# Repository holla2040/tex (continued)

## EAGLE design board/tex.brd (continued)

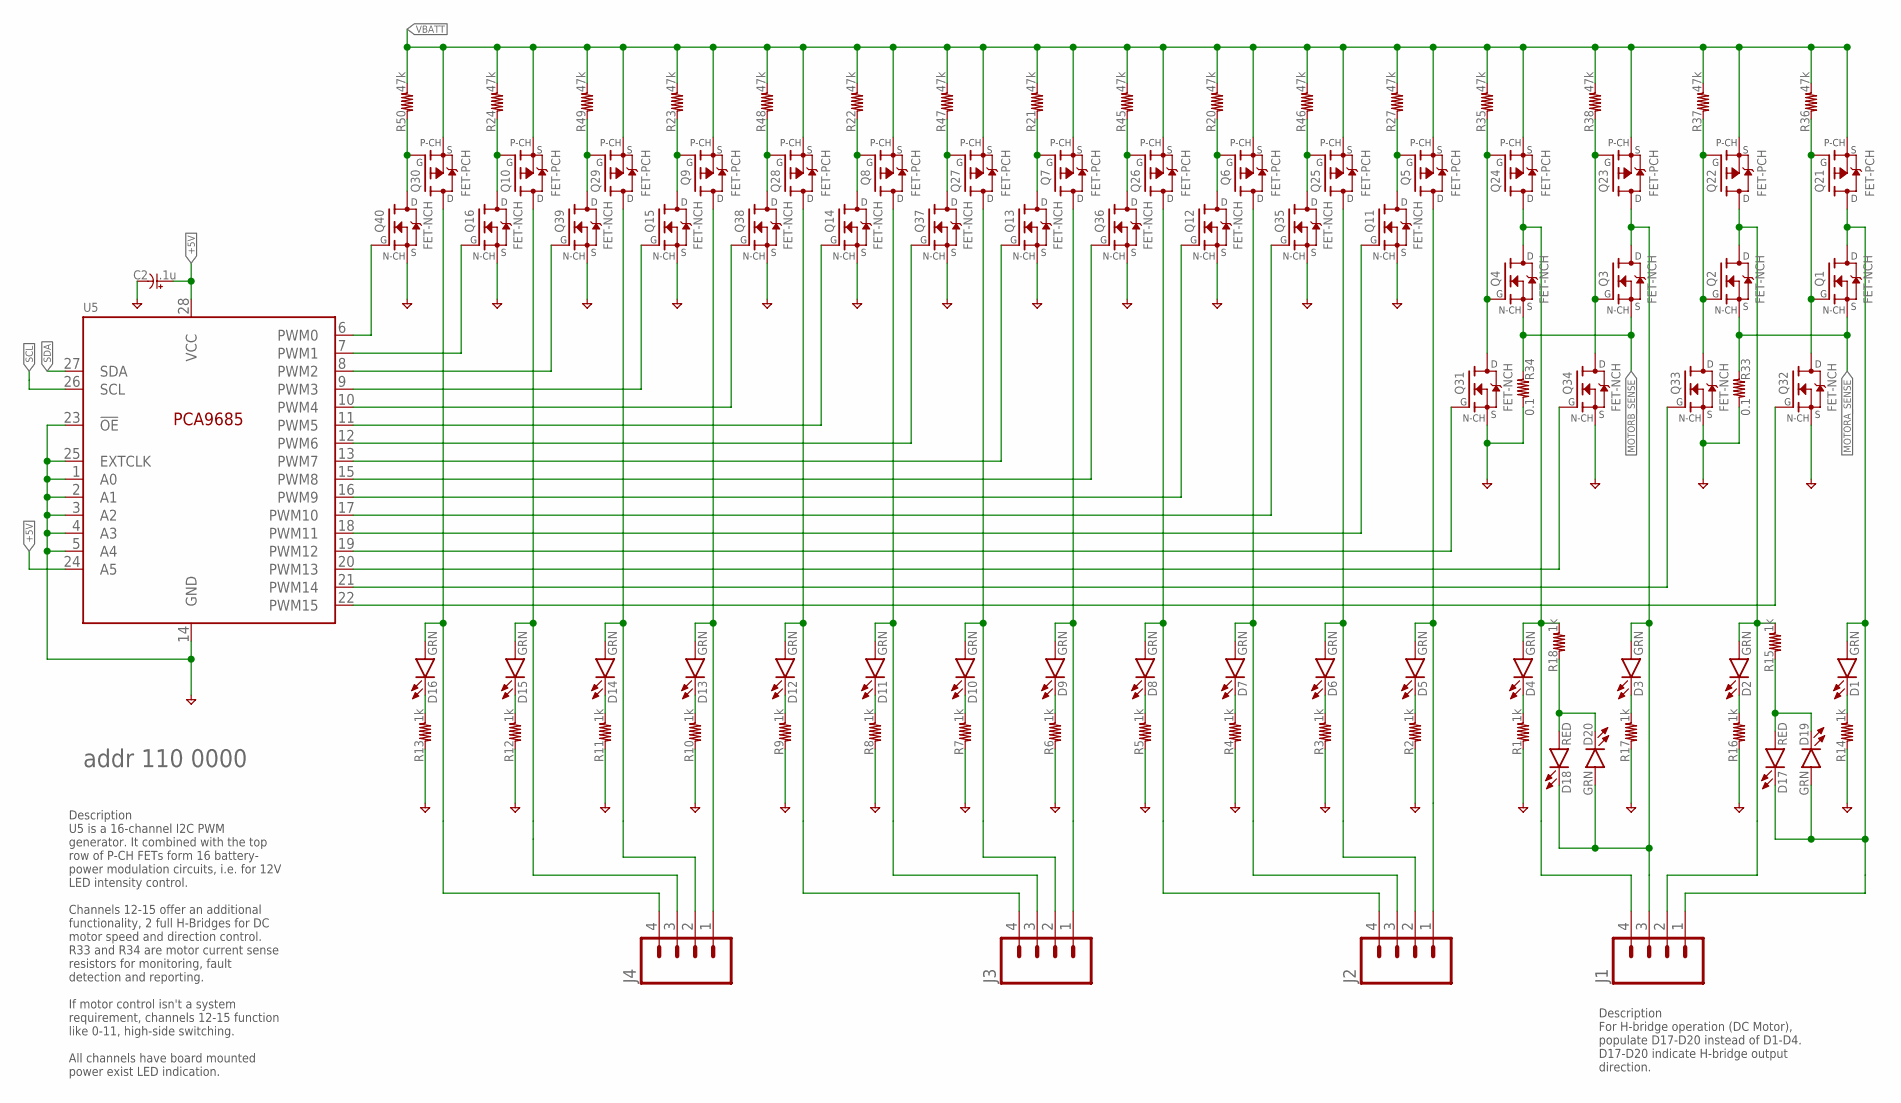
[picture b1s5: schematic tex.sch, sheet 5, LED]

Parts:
C2: .1u; C0603
D1, D2, D3, D4, D5, D6, D7, D8, D9, D10, D11, D12, D13, D14, D15, D16, D19, D20: GRN; LED0603
D17, D18: RED; LED0603
J1, J2, J3, J4: CONN-04-PLUGIN-SCREW; CONN-3.81MM-KF2EDG-4
Q1, Q2, Q3, Q4: FET-NCH; TO252
Q5, Q6, Q7, Q8, Q9, Q10, Q21, Q22, Q23, Q24, Q25, Q26, Q27, Q28, Q29, Q30: FET-PCH; TO252
Q11, Q12, Q13, Q14, Q15, Q16, Q31, Q32, Q33, Q34, Q35, Q36, Q37, Q38, Q39, Q40: FET-NCH; SOT23-3
R1, R2, R3, R4, R5, R6, R7, R8, R9, R10, R11, R12, R13, R14, R15, R16, R17, R18: 1k; R0603
R20, R21, R22, R23, R24, R27, R35, R36, R37, R38, R45, R46, R47, R48, R49, R50: 47k; R0603
R33, R34: 0.1; R1210
U5: PCA9685; TSSOP28

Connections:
+5V: C2.1, U5.24 (A5), U5.28 (VCC); also elsewhere on the board
GND: C2.2, Q11.2 (S), Q12.2 (S), Q13.2 (S), Q14.2 (S), Q15.2 (S), Q16.2 (S), Q31.2 (S), Q32.2 (S), Q33.2 (S), Q34.2 (S), Q35.2 (S), Q36.2 (S), Q37.2 (S), Q38.2 (S), Q39.2 (S), Q40.2 (S), R1.1, R2.1, R3.1, R4.1, R5.1, R6.1, R7.1, R8.1, R9.1, R10.1, R11.1, R12.1, R13.1, R14.1, R16.1, R17.1, R33.2, R34.2, U5.1 (A0), U5.2 (A1), U5.3 (A2), U5.4 (A3), U5.5 (A4), U5.14 (GND), U5.23 (!OE), U5.25 (EXTCLK); also elsewhere on the board
MOTORA_SENSE: Q1.2 (S), Q2.2 (S), R33.1; also elsewhere on the board
MOTORB_SENSE: Q3.2 (S), Q4.2 (S), R34.1; also elsewhere on the board
unnamed: Q40.1 (G), U5.6 (PWM0)
unnamed: Q6.1 (G), Q12.3 (D), R20.1
unnamed: Q26.1 (G), Q36.3 (D), R45.1
unnamed: Q7.1 (G), Q13.3 (D), R21.1
unnamed: Q27.1 (G), Q37.3 (D), R47.1
unnamed: Q8.1 (G), Q14.3 (D), R22.1
unnamed: Q28.1 (G), Q38.3 (D), R48.1
unnamed: Q9.1 (G), Q15.3 (D), R23.1
unnamed: Q29.1 (G), Q39.3 (D), R49.1
unnamed: Q10.1 (G), Q16.3 (D), R24.1
unnamed: Q30.1 (G), Q40.3 (D), R50.1
unnamed: Q16.1 (G), U5.7 (PWM1)
unnamed: Q39.1 (G), U5.8 (PWM2)
unnamed: Q15.1 (G), U5.9 (PWM3)
unnamed: Q38.1 (G), U5.10 (PWM4)
unnamed: Q14.1 (G), U5.11 (PWM5)
unnamed: Q37.1 (G), U5.12 (PWM6)
unnamed: Q13.1 (G), U5.13 (PWM7)
unnamed: Q36.1 (G), U5.15 (PWM8)
unnamed: Q12.1 (G), U5.16 (PWM9)
unnamed: D2.A, J1.2, Q2.3 (D), Q22.3 (D), R15.2
unnamed: Q2.1 (G), Q22.1 (G), Q33.3 (D), R37.1
unnamed: D1.A, D17.C, D19.A, J1.1, Q1.3 (D), Q21.3 (D)
unnamed: Q1.1 (G), Q21.1 (G), Q32.3 (D), R36.1
unnamed: Q32.1 (G), U5.22 (PWM15)
unnamed: Q33.1 (G), U5.21 (PWM14)
unnamed: D4.A, J1.4, Q4.3 (D), Q24.3 (D), R18.2
unnamed: Q4.1 (G), Q24.1 (G), Q31.3 (D), R35.1
unnamed: D16.A, J4.4, Q30.3 (D)
unnamed: D15.A, J4.3, Q10.3 (D)
unnamed: D14.A, J4.2, Q29.3 (D)
unnamed: D13.A, J4.1, Q9.3 (D)
unnamed: D12.A, J3.4, Q28.3 (D)
unnamed: D11.A, J3.3, Q8.3 (D)
unnamed: D10.A, J3.2, Q27.3 (D)
unnamed: D9.A, J3.1, Q7.3 (D)
unnamed: D8.A, J2.4, Q26.3 (D)
unnamed: D7.A, J2.3, Q6.3 (D)
unnamed: D13.C, R10.2
unnamed: D12.C, R9.2
unnamed: D1.C, R14.2
unnamed: D2.C, R16.2
unnamed: D3.C, R17.2
unnamed: D4.C, R1.2
unnamed: D14.C, R11.2
unnamed: D15.C, R12.2
unnamed: D16.C, R13.2
unnamed: D3.A, D18.C, D20.A, J1.3, Q3.3 (D), Q23.3 (D)
unnamed: Q3.1 (G), Q23.1 (G), Q34.3 (D), R38.1
unnamed: Q34.1 (G), U5.20 (PWM13)
unnamed: Q31.1 (G), U5.19 (PWM12)
unnamed: D18.A, D20.C, R18.1
unnamed: Q35.1 (G), U5.17 (PWM10)
unnamed: Q11.1 (G), U5.18 (PWM11)
unnamed: D17.A, D19.C, R15.1
unnamed: D6.A, J2.2, Q25.3 (D)
unnamed: D5.A, J2.1, Q5.3 (D)
unnamed: Q5.1 (G), Q11.3 (D), R27.1
unnamed: Q25.1 (G), Q35.3 (D), R46.1
unnamed: D5.C, R2.2
unnamed: D6.C, R3.2
unnamed: D7.C, R4.2
unnamed: D8.C, R5.2
unnamed: D9.C, R6.2
unnamed: D10.C, R7.2
unnamed: D11.C, R8.2
SCL: U5.26 (SCL); also elsewhere on the board
SDA: U5.27 (SDA); also elsewhere on the board
VBATT: Q5.2 (S), Q6.2 (S), Q7.2 (S), Q8.2 (S), Q9.2 (S), Q10.2 (S), Q21.2 (S), Q22.2 (S), Q23.2 (S), Q24.2 (S), Q25.2 (S), Q26.2 (S), Q27.2 (S), Q28.2 (S), Q29.2 (S), Q30.2 (S), R20.2, R21.2, R22.2, R23.2, R24.2, R27.2, R35.2, R36.2, R37.2, R38.2, R45.2, R46.2, R47.2, R48.2, R49.2, R50.2; also elsewhere on the board

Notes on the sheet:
addr 110 0000
Description U5 is a 16-channel I2C PWM generator. It combined with the top row of P-CH FETs form 16 battery- power modulation circuits, i.e. for 12V LED intensity control. Channels 12-15 offer an additional functionality, 2 full H-Bridges for DC motor speed and direction control. R33 and R34 are mo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
Description For H-bridge operation (DC Motor), populate D17-D20 instead of D1-D4. D17-D20 indicate H-bridge output direction.

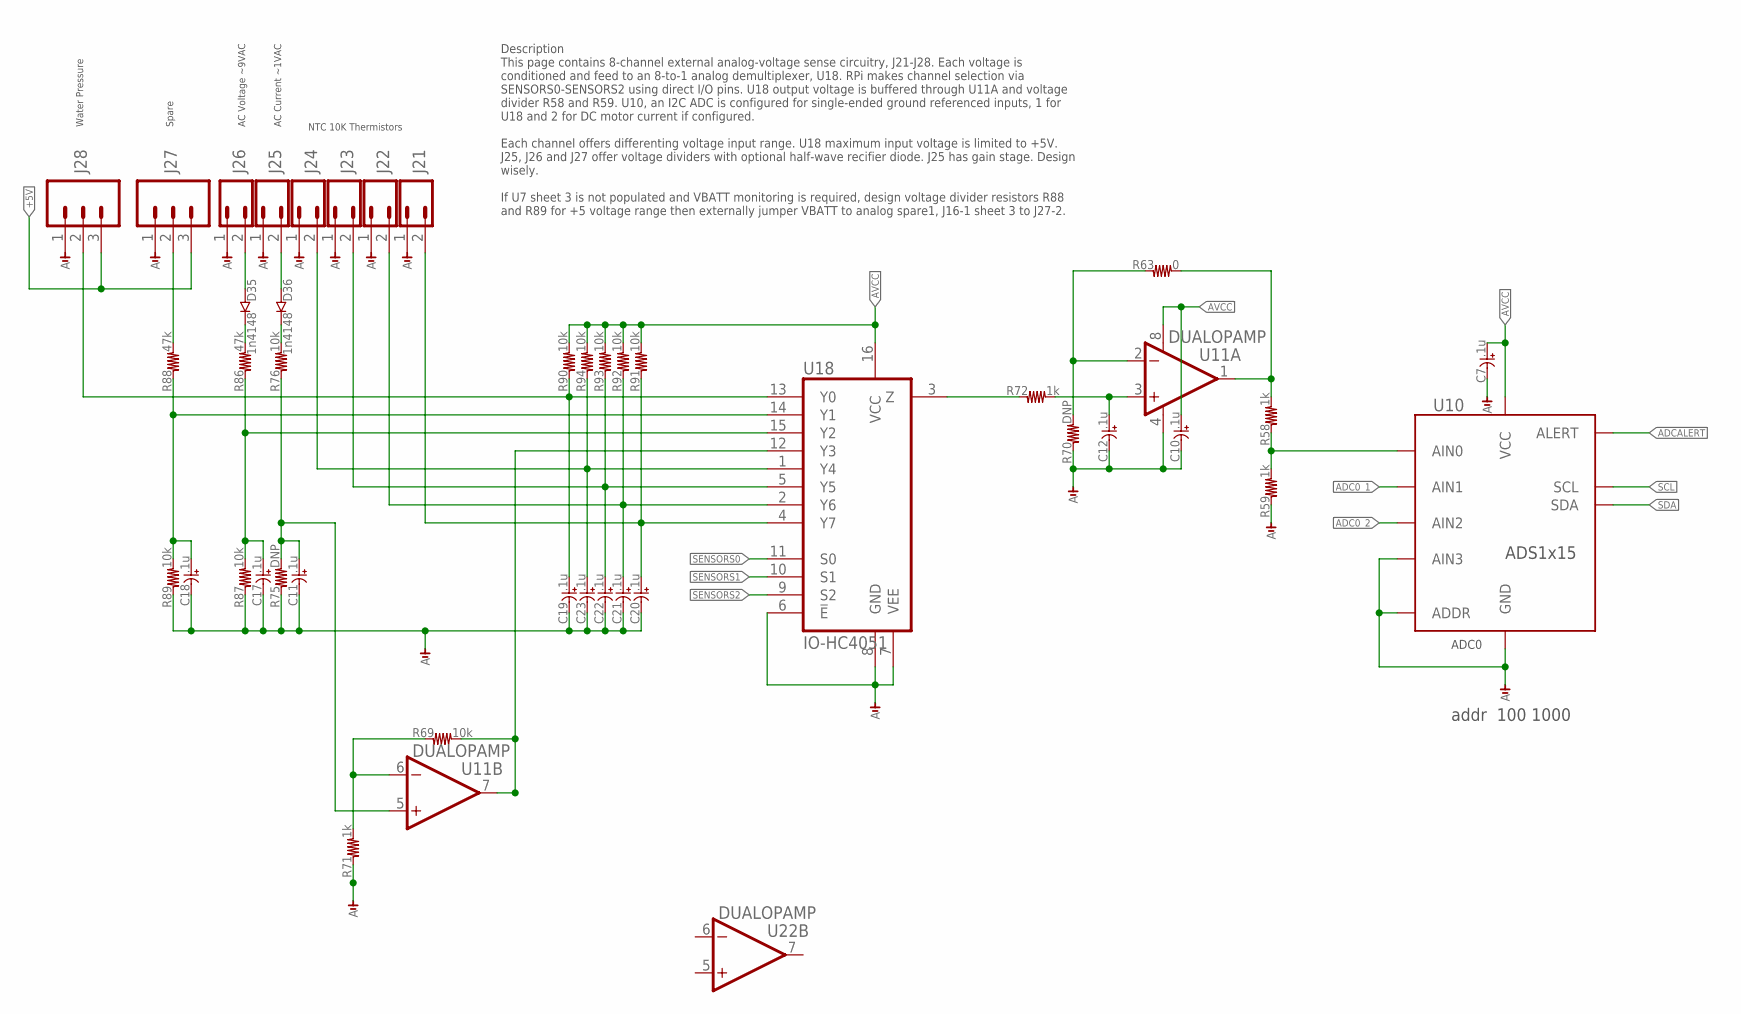
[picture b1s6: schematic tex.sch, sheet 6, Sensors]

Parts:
C7, C10, C11, C12, C17, C18, C19, C20, C21, C22, C23: .1u; C0603
D35, D36: 1n4148; SOD-523
J21, J22, J23, J24, J25, J26: CONN-02-PLUGIN-SCREW; CONN-3.81MM-KF2EDG-2
J27, J28: CONN-03-PLUGIN-SCREW; CONN-3.81MM-KF2EDG-3
R58, R59, R71, R72: 1k; R0603
R63: 0; R0603
R69, R76, R87, R89, R90, R91, R92, R93, R94: 10k; R0603
R70, R75: DNP; R0603
R86, R88: 47k; R0603
U10: ADS1x15; MSOP10_0.5
U11, U22: DUALOPAMP; SO08
U18: IO-HC4051; SO16

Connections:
+5V: J27.3, J28.3; also elsewhere on the board
ADC0_1: U10.5 (AIN1); also elsewhere on the board
ADC0_2: U10.6 (AIN2); also elsewhere on the board
ADCALERT: U10.2 (ALERT); also elsewhere on the board
AGND: C7.2, C10.2, C11.2, C12.2, C17.2, C18.2, C19.2, C20.2, C21.2, C22.2, C23.2, J21.1, J22.1, J23.1, J24.1, J25.1, J26.1, J27.1, J28.1, R59.1, R70.1, R71.1, R75.1, R87.1, R89.1, U10.1 (ADDR), U10.3 (GND), U10.7 (AIN3), U11.4 (V-), U18.6 (!E), U18.7 (VEE), U18.8 (GND); also elsewhere on the board
AVCC: C7.1, C10.1, R90.2, R91.2, R92.2, R93.2, R94.2, U10.8 (VCC), U11.8 (V+), U18.16 (VCC); also elsewhere on the board
unnamed: D35.C, R86.2
unnamed: D35.A, J26.2
unnamed: D36.C, R76.2
unnamed: D36.A, J25.2
unnamed: J27.2, R88.2
unnamed: R63.1, R70.2, U11.2 (-IN)
unnamed: R69.1, R71.2, U11.6 (-IN)
unnamed: C12.1, R72.2, U11.3 (+IN)
unnamed: C19.1, J28.2, R90.1, U18.13 (Y0)
unnamed: C18.1, R88.1, R89.2, U18.14 (Y1)
unnamed: C17.1, R86.1, R87.2, U18.15 (Y2)
unnamed: C11.1, R75.2, R76.1, U11.5 (+IN)
unnamed: C23.1, J24.2, R94.1, U18.1 (Y4)
unnamed: C22.1, J23.2, R93.1, U18.5 (Y5)
unnamed: C21.1, J22.2, R92.1, U18.2 (Y6)
unnamed: C20.1, J21.2, R91.1, U18.4 (Y7)
unnamed: R58.2, R63.2, U11.1 (OUT)
unnamed: R72.1, U18.3 (Z)
unnamed: R58.1, R59.2, U10.4 (AIN0)
unnamed: R69.2, U11.7 (OUT), U18.12 (Y3)
SCL: U10.10 (SCL); also elsewhere on the board
SDA: U10.9 (SDA); also elsewhere on the board
SENSORS0: U18.11 (S0); also elsewhere on the board
SENSORS1: U18.10 (S1); also elsewhere on the board
SENSORS2: U18.9 (S2); also elsewhere on the board
V+: U22.8 (V+)
V-: U22.4 (V-)

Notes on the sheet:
ADC0
NTC 10K Thermistors
Water Pressure
Spare
AC Voltage ~9VAC
AC Current ~1VAC
addr 100 1000
Description This page contains 8-channel external analog-voltage sense circuitry, J21-J28. Each voltage is conditioned and feed to an 8-to-1 analog demultiplexer, U18. RPi makes channel selection via SENSORS0-SENSORS2 using direct I/O pins. U18 output voltage is buffered through U11A and voltage di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

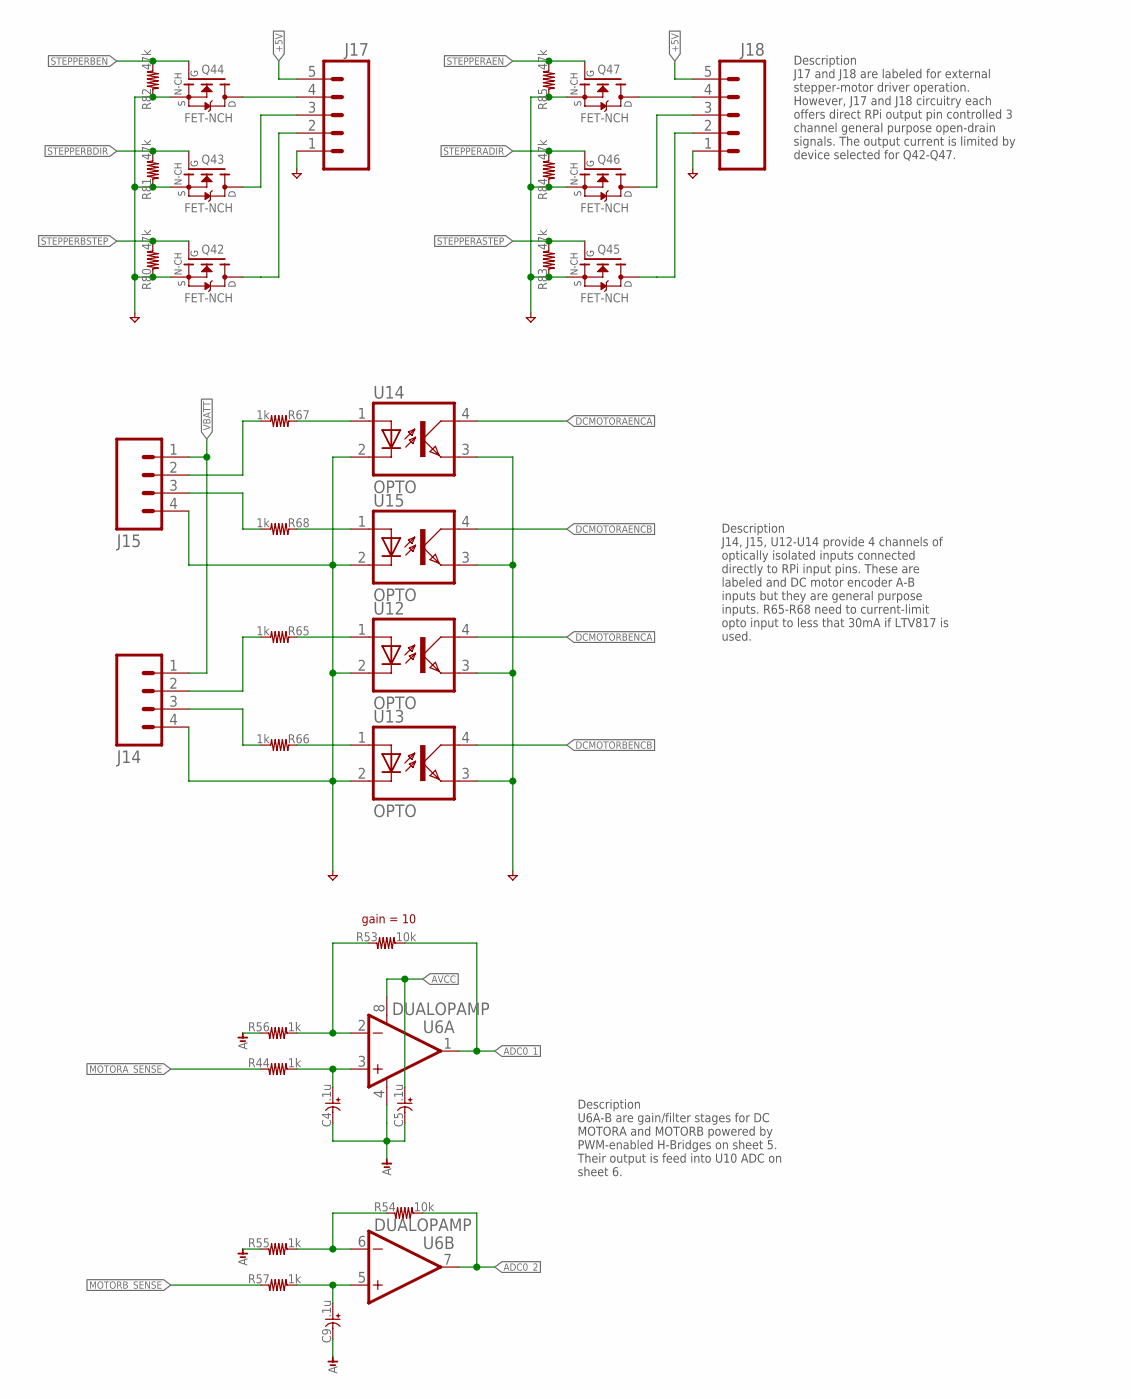
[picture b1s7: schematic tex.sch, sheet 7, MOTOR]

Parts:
C4, C5, C9: .1u; C0603
J14, J15: CONN-04-PLUGIN-SCREW; CONN-3.81MM-KF2EDG-4
J17, J18: CONN-05-PLUGIN-SCREW; CONN-3.81MM-KF2EDG-5
Q42, Q43, Q44, Q45, Q46, Q47: FET-NCH; SOT23-3
R44, R55, R56, R57, R65, R66, R67, R68: 1k; R0603
R53, R54: 10k; R0603
R80, R81, R82, R83, R84, R85: 47k; R0603
U6: DUALOPAMP; SO08
U12, U13, U14, U15: OPTO; LTV817

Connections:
+5V: J17.5, J18.5; also elsewhere on the board
ADC0_1: R53.2, U6.1 (OUT); also elsewhere on the board
ADC0_2: R54.2, U6.7 (OUT); also elsewhere on the board
AGND: C4.2, C5.2, C9.2, R55.1, R56.1, U6.4 (V-); also elsewhere on the board
AVCC: C5.1, U6.8 (V+); also elsewhere on the board
DCMOTORAENCA: U14.4; also elsewhere on the board
DCMOTORAENCB: U15.4; also elsewhere on the board
DCMOTORBENCA: U12.4; also elsewhere on the board
DCMOTORBENCB: U13.4; also elsewhere on the board
GND: J14.4, J15.4, J17.1, J18.1, Q42.2 (S), Q43.2 (S), Q44.2 (S), Q45.2 (S), Q46.2 (S), Q47.2 (S), R80.1, R81.1, R82.1, R83.1, R84.1, R85.1, U12.2, U12.3, U13.2, U13.3, U14.2, U14.3, U15.2, U15.3; also elsewhere on the board
MOTORA_SENSE: R44.1; also elsewhere on the board
MOTORB_SENSE: R57.1; also elsewhere on the board
unnamed: C4.1, R44.2, U6.3 (+IN)
unnamed: R54.1, R55.2, U6.6 (-IN)
unnamed: R53.1, R56.2, U6.2 (-IN)
unnamed: C9.1, R57.2, U6.5 (+IN)
unnamed: R67.1, U14.1
unnamed: J15.3, R68.2
unnamed: J15.2, R67.2
unnamed: J17.2, Q42.3 (D)
unnamed: J18.4, Q47.3 (D)
unnamed: J18.3, Q46.3 (D)
unnamed: J18.2, Q45.3 (D)
unnamed: R68.1, U15.1
unnamed: J14.2, R65.2
unnamed: J14.3, R66.2
unnamed: R65.1, U12.1
unnamed: R66.1, U13.1
STEPPER1DIROUT: J17.3, Q43.3 (D)
STEPPER1ENOUT: J17.4, Q44.3 (D)
STEPPERADIR: Q46.1 (G), R84.2; also elsewhere on the board
STEPPERAEN: Q47.1 (G), R85.2; also elsewhere on the board
STEPPERASTEP: Q45.1 (G), R83.2; also elsewhere on the board
STEPPERBDIR: Q43.1 (G), R81.2; also elsewhere on the board
STEPPERBEN: Q44.1 (G), R82.2; also elsewhere on the board
STEPPERBSTEP: Q42.1 (G), R80.2; also elsewhere on the board
VBATT: J14.1, J15.1; also elsewhere on the board

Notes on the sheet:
gain = 10
Description J17 and J18 are labeled for external stepper-motor driver operation. However, J17 and J18 circuitry each offers direct RPi output pin controlled 3 channel general purpose open-drain signals. The output current is limited by device selected for Q42-Q47.
Description J14, J15, U12-U14 provide 4 channels of optically isolated inputs connected directly to RPi input pins. These are labeled and DC motor encoder A-B inputs but they are general purpose inputs. R65-R68 need to current-limit opto input to less that 30mA if LTV817 is used.
Description U6A-B are gain/filter stages for DC MOTORA and MOTORB powered by PWM-enabled H-Bridges on sheet 5. Their output is feed into U10 ADC on sheet 6.

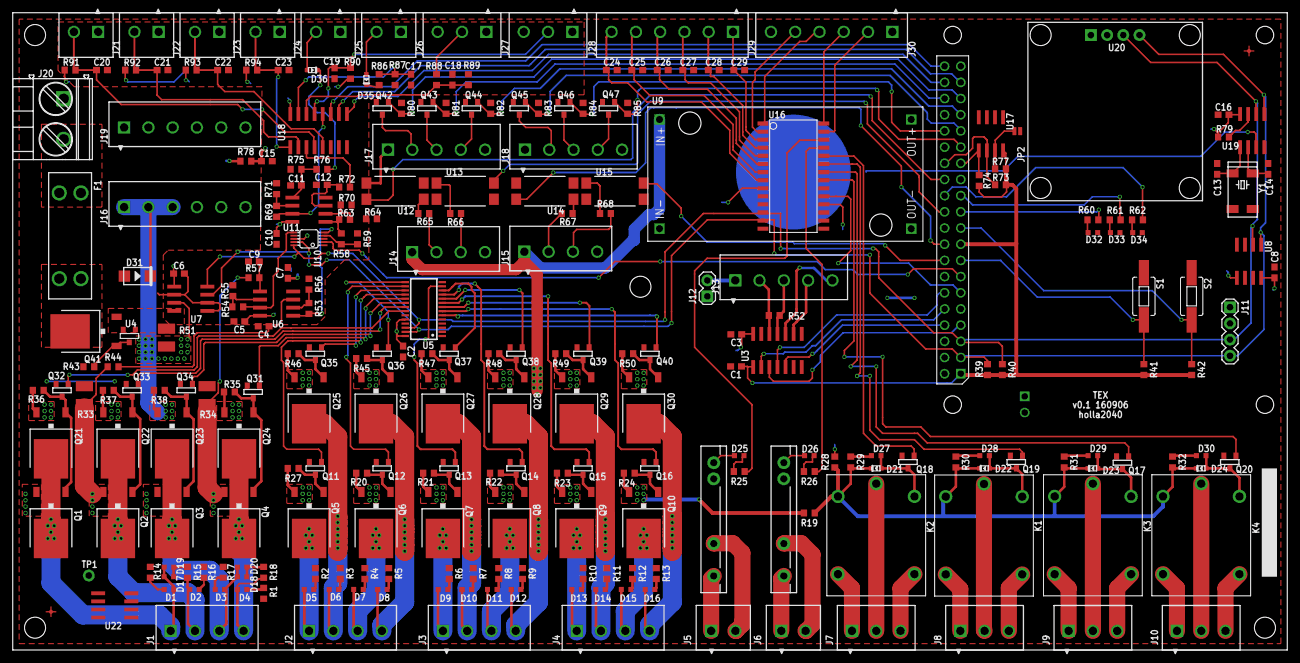
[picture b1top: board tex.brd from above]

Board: 2 copper layers, 200.0 x 100.0 mm, 271 parts (1 on the bottom side), 204 nets.

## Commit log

2015-11-07 initial add
2015-11-07 added p-ch selection info
2015-11-07 updated p-ch choices
2015-11-07 added initial lighting requirements
2016-01-11 initial add for most
2016-01-11 added turbine tab
2016-03-02 added notes on pwm control
2016-03-04 added parts to pwm output sheet
2016-08-23 continuing work on sch
2016-08-27 mostly layout changes
2016-09-06 parts placed
2016-09-06 started routing changed rtc to MCP to have vbat
2016-09-06 routing
2016-09-06 routing complete
2016-09-07 ready to place names
2016-09-07 board file submission
2016-09-07 found silk issues, tex-v0.1-gerber.zip submitted for production
2016-09-19 added todo section
2016-09-27 set R and C values
2016-09-28 added functionality section
2016-11-28 changed connectors to match new lib naming
2016-11-28 swapped relays for new part in holla lib
2018-11-12 added descriptions to all circuit elements, generated update schematic
2019-04-06 added part number
2019-04-06 getting ready for first board run
2019-04-12 initial add for blink
2019-04-12 wrong manufacturer of lm75
2019-04-12 io now counting to include the ssr control
2019-04-19 added a couple comments
2019-04-19 fixed SSR relay logic
2019-04-19 deleting these
2019-04-19 much simplier version
2019-04-19 now much simplier
2019-04-19 removed unused comments and code
2019-04-20 "PCA9685.py: Added handeling of KeyboardInterrupt exception"
2019-04-20 initial add for ip
2019-04-20 added exception handling if interface has no ip address
2019-04-20 added startup note
2019-04-20 changing the display code
2019-04-20 added todo items
2019-04-20 added more notes
2019-04-20 more notes
2019-04-20 simplify
2019-04-21 .gitignore: initial commit of file
2019-04-21 "led2.py: inital commit of file"
2019-04-22 update notes from last sd card build
2019-05-02 ".gitignore: Fixed #*# to \#*#"
2019-05-02 Initial import of these files
2019-05-02 "led2_adafruit.py: Initial commit"
2019-05-02 "led2_adafruit.py: Got it to work"
2019-05-02 almost working
2019-05-02 first working version
2019-05-03 "display_stats.py: bug fixes"
2019-05-03 "temperatureSensor.py: Added get for C and F and better printing"
2019-05-03 Initial commit of files
2019-05-04 Adding code
2019-05-04 Initial commit of file
2019-05-04 humanTestFeedback.py: Got it to work stand alone
2019-05-04 renamed: ina219.py -> lib/ina219.py, lib_oled96.py -> lib/lib_oled96.py
2019-05-04 ".gitignore: Added *.pyc"
2019-05-04 "humanTestFeedback.py, testTexInterface.py: Got first humanTest to work!"
2019-05-05 "testTexInterface.py, texInterface.py: Continuing to add tests"
2019-05-05 Adding tests, working out the kinks
2019-05-05 "testTexInterface.py: Simplifying testBlueLed"
2019-05-06 "led2_adafruit.py: Removed unneeded smbus import"
2019-05-06 "texInterface.py, testTexInterface.py: Added led controller"
2019-05-07 "testTexInterface.py, texInterface.py: Interim checkin"
2019-05-07 "testTexInterface.py: Putting RGB LED tests in order"
2019-05-07 "humanTestFeedback.py: Removed hard-coded / from path"
2019-05-07 "testTexInterface.py, texInterface.py: Added current/power monitor functionality and tests"
2019-05-10 "testTexInterface.py: Added more human tests"
2019-05-10 "testTexInterface.py: Seperated human and non-human tests using base class"
2019-05-12 "texInterface.py: added Class LIGHT_LEVEL so like an enum"
2019-05-12 "lights.py, testLights.py: Initial commit"
2019-05-12 "testLights.py: Added testGetLightMode"
2019-05-12 "lights.py: Added DecayLight class. Parses, but has not been tested at all"
2019-05-13 testLights.py -> testLight.py
2019-05-13 "lights.py: Added DecayLight and various fixes"
2019-05-13 "lights.py: Added self.lightLevel back in"
2019-05-13 "testLight.py: Tweeks, additions, etc"
2019-05-13 "texInterface.py: LIGHT_LEVEL -> PWM_LIGHT_LEVEL"
2019-05-14 "lights.py: When decaying, set light level to 0 when below .0075 to look more realistic"
2019-05-14 "shoeBoxF16.py: Now calcuates needed sleep time between loops based on elapsed time"
